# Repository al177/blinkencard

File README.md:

# blinkencard
FPGA based blinky computer emulator

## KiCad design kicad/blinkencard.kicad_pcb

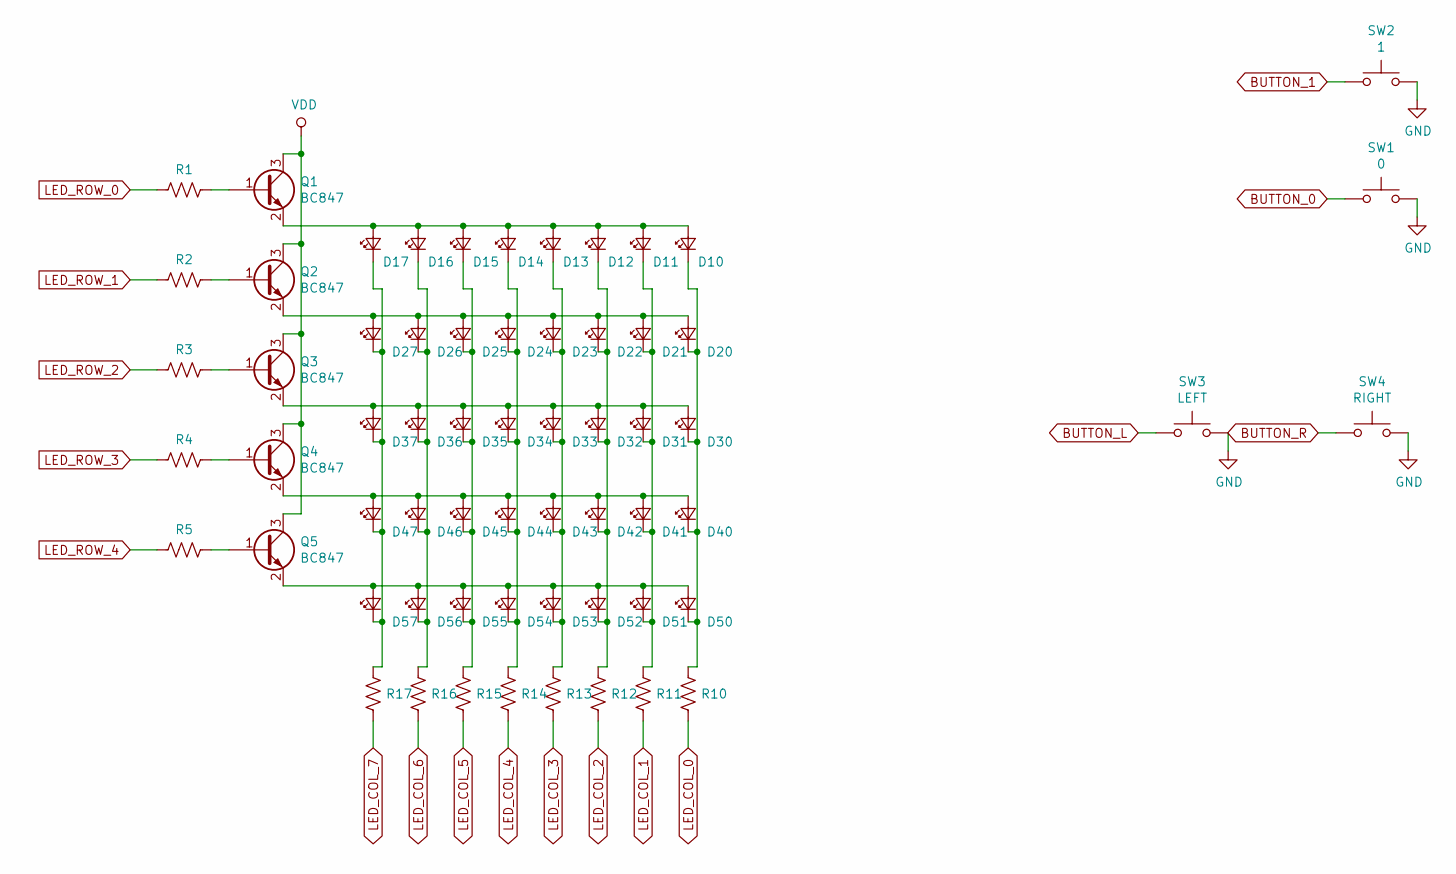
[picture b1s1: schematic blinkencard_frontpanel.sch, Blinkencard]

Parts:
D10, D11, D12, D13, D14, D15, D16, D17, D20, D21, D22, D23, D24, D25, D26, D27, D30, D31, D32, D33, D34, D35, D36, D37, D40, D41, D42, D43, D44, D45, D46, D47, D50, D51, D52, D53, D54, D55, D56, D57: LED_Small; LED_1206_3216Metric_ReverseMount_Hole1.8x2.4mm; mfg_part LTST-C230KRKT
Q1, Q2, Q3, Q4, Q5: BC847; SOT-23; mfg_part BC847CLT1G
R1, R2, R3, R4, R5: 10K; R_0603_1608Metric; mfg_part RC0603JR-0710KL
R10, R11, R12, R13, R14, R15, R16, R17: 270; R_0603_1608Metric; mfg_part RMCF0603JT270R
SW1: 0; SW_SPST_PTS645; mfg_part PTS645SM50SMTR92 LFS
SW2: 1; SW_SPST_PTS645; mfg_part PTS645SM50SMTR92 LFS
SW3: LEFT; SW_SPST_PTS645; mfg_part PTS645SM50SMTR92 LFS
SW4: RIGHT; SW_SPST_PTS645; mfg_part PTS645SM50SMTR92 LFS

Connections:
BUTTON_0: SW1.1; also elsewhere on the board
BUTTON_1: SW2.1; also elsewhere on the board
BUTTON_L: SW3.1; also elsewhere on the board
BUTTON_R: SW4.1; also elsewhere on the board
GND: SW1.2, SW2.2, SW3.2, SW4.2; also elsewhere on the board
LED_COL_0: R10.2; also elsewhere on the board
LED_COL_1: R11.2; also elsewhere on the board
LED_COL_2: R12.2; also elsewhere on the board
LED_COL_3: R13.2; also elsewhere on the board
LED_COL_4: R14.2; also elsewhere on the board
LED_COL_5: R15.2; also elsewhere on the board
LED_COL_6: R16.2; also elsewhere on the board
LED_COL_7: R17.2; also elsewhere on the board
LED_ROW_0: R1.2; also elsewhere on the board
LED_ROW_1: R2.2; also elsewhere on the board
LED_ROW_2: R3.2; also elsewhere on the board
LED_ROW_3: R4.2; also elsewhere on the board
LED_ROW_4: R5.2; also elsewhere on the board
unnamed: D10.1 (K), D20.1 (K), D30.1 (K), D40.1 (K), D50.1 (K), R10.1
unnamed: D10.2 (A), D11.2 (A), D12.2 (A), D13.2 (A), D14.2 (A), D15.2 (A), D16.2 (A), D17.2 (A), Q1.2 (E)
unnamed: D11.1 (K), D21.1 (K), D31.1 (K), D41.1 (K), D51.1 (K), R11.1
unnamed: D12.1 (K), D22.1 (K), D32.1 (K), D42.1 (K), D52.1 (K), R12.1
unnamed: D13.1 (K), D23.1 (K), D33.1 (K), D43.1 (K), D53.1 (K), R13.1
unnamed: D14.1 (K), D24.1 (K), D34.1 (K), D44.1 (K), D54.1 (K), R14.1
unnamed: D15.1 (K), D25.1 (K), D35.1 (K), D45.1 (K), D55.1 (K), R15.1
unnamed: D16.1 (K), D26.1 (K), D36.1 (K), D46.1 (K), D56.1 (K), R16.1
unnamed: D17.1 (K), D27.1 (K), D37.1 (K), D47.1 (K), D57.1 (K), R17.1
unnamed: D20.2 (A), D21.2 (A), D22.2 (A), D23.2 (A), D24.2 (A), D25.2 (A), D26.2 (A), D27.2 (A), Q2.2 (E)
unnamed: D30.2 (A), D31.2 (A), D32.2 (A), D33.2 (A), D34.2 (A), D35.2 (A), D36.2 (A), D37.2 (A), Q3.2 (E)
unnamed: D40.2 (A), D41.2 (A), D42.2 (A), D43.2 (A), D44.2 (A), D45.2 (A), D46.2 (A), D47.2 (A), Q4.2 (E)
unnamed: D50.2 (A), D51.2 (A), D52.2 (A), D53.2 (A), D54.2 (A), D55.2 (A), D56.2 (A), D57.2 (A), Q5.2 (E)
unnamed: Q1.1 (B), R1.1
unnamed: Q2.1 (B), R2.1
unnamed: Q3.1 (B), R3.1
unnamed: Q4.1 (B), R4.1
unnamed: Q5.1 (B), R5.1
VDD: Q1.3 (C), Q2.3 (C), Q3.3 (C), Q4.3 (C), Q5.3 (C); also elsewhere on the board

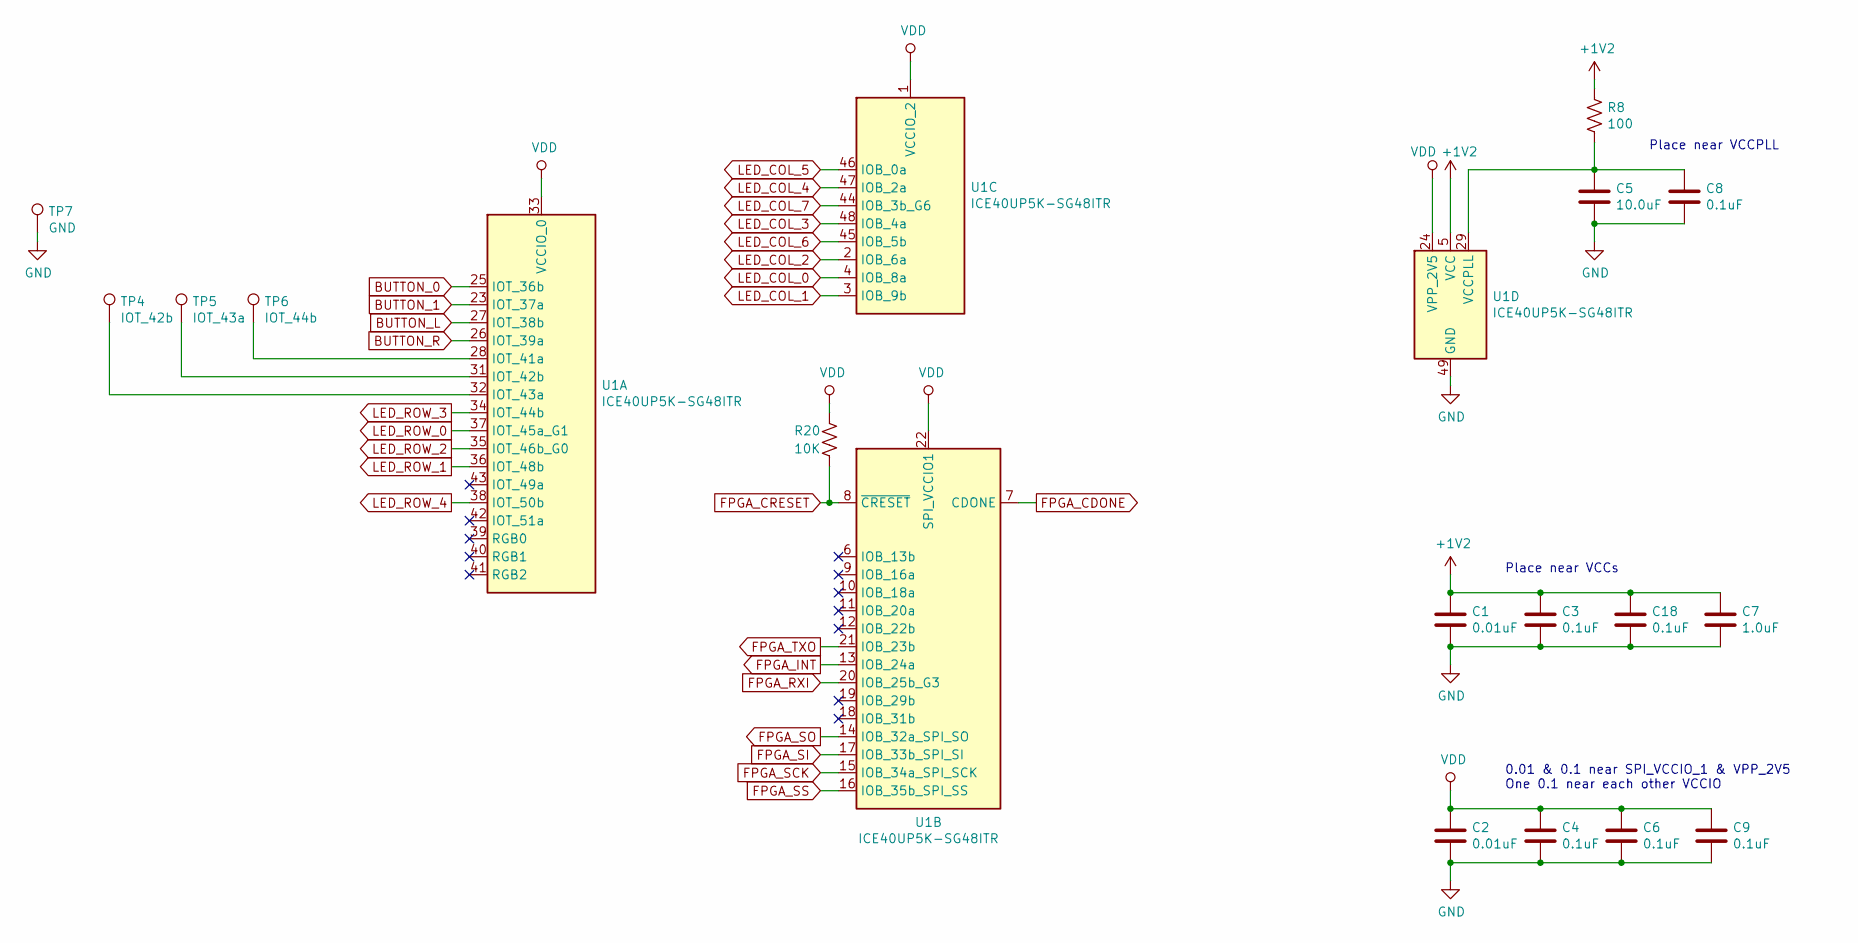
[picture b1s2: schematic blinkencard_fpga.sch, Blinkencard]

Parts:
C1, C2: 0.01uF; C_0603_1608Metric; mfg_part CL21B103KBANNNC
C3, C4, C6, C8, C9, C18: 0.1uF; C_0603_1608Metric; mfg_part CL10F104ZO8NNNC
C5: 10.0uF; C_0805_2012Metric; mfg_part CL21A106KQCLRNC
C7: 1.0uF; C_0805_2012Metric; mfg_part CL21B105KOFNNNG
R8: 100; R_0603_1608Metric; mfg_part RC0603JR-07100RL
R20: 10K; R_0603_1608Metric; mfg_part RC0603JR-0710KL
TP4: IOT_42b; TestPoint_Pad_D1.5mm; mfg_part NP
TP5: IOT_43a; TestPoint_Pad_D1.5mm; mfg_part NP
TP6: IOT_44b; TestPoint_Pad_D1.5mm; mfg_part NP
TP7: GND; TestPoint_Pad_D1.5mm; mfg_part NP
U1: ICE40UP5K-SG48ITR; QFN-48-1EP_7x7mm_P0.5mm_EP5.15x5.15mm_ThermalVias; mfg_part ICE40UP5K-SG48I

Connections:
+1V2: C1.1, C3.1, C7.1, C18.1, R8.1, U1.5 (VCC), U1.30 (VCC); also elsewhere on the board
BUTTON_0: U1.25 (IOT_36b); also elsewhere on the board
BUTTON_1: U1.23 (IOT_37a); also elsewhere on the board
BUTTON_L: U1.27 (IOT_38b); also elsewhere on the board
BUTTON_R: U1.26 (IOT_39a); also elsewhere on the board
FPGA_CDONE: U1.7 (CDONE); also elsewhere on the board
FPGA_CRESET: R20.2, U1.8 (~CRESET); also elsewhere on the board
FPGA_INT: U1.13 (IOB_24a); also elsewhere on the board
FPGA_RXI: U1.20 (IOB_25b_G3); also elsewhere on the board
FPGA_SCK: U1.15 (IOB_34a_SPI_SCK); also elsewhere on the board
FPGA_SI: U1.17 (IOB_33b_SPI_SI); also elsewhere on the board
FPGA_SO: U1.14 (IOB_32a_SPI_SO); also elsewhere on the board
FPGA_SS: U1.16 (IOB_35b_SPI_SS); also elsewhere on the board
FPGA_TXO: U1.21 (IOB_23b); also elsewhere on the board
GND: C1.2, C2.2, C3.2, C4.2, C5.2, C6.2, C7.2, C8.2, C9.2, C18.2, TP7.1, U1.49 (GND); also elsewhere on the board
LED_COL_0: U1.4 (IOB_8a); also elsewhere on the board
LED_COL_1: U1.3 (IOB_9b); also elsewhere on the board
LED_COL_2: U1.2 (IOB_6a); also elsewhere on the board
LED_COL_3: U1.48 (IOB_4a); also elsewhere on the board
LED_COL_4: U1.47 (IOB_2a); also elsewhere on the board
LED_COL_5: U1.46 (IOB_0a); also elsewhere on the board
LED_COL_6: U1.45 (IOB_5b); also elsewhere on the board
LED_COL_7: U1.44 (IOB_3b_G6); also elsewhere on the board
LED_ROW_0: U1.37 (IOT_45a_G1); also elsewhere on the board
LED_ROW_1: U1.36 (IOT_48b); also elsewhere on the board
LED_ROW_2: U1.35 (IOT_46b_G0); also elsewhere on the board
LED_ROW_3: U1.34 (IOT_44b); also elsewhere on the board
LED_ROW_4: U1.38 (IOT_50b); also elsewhere on the board
unnamed: C5.1, C8.1, R8.2, U1.29 (VCCPLL)
unnamed: TP4.1, U1.32 (IOT_43a)
unnamed: TP5.1, U1.31 (IOT_42b)
unnamed: TP6.1, U1.28 (IOT_41a)
VDD: C2.1, C4.1, C6.1, C9.1, R20.1, U1.1 (VCCIO_2), U1.22 (SPI_VCCIO1), U1.24 (VPP_2V5), U1.33 (VCCIO_0); also elsewhere on the board

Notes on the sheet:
0.01 & 0.1 near SPI_VCCIO_1 & VPP_2V5 One 0.1 near each other VCCIO
Place near VCCs
Place near VCCPLL

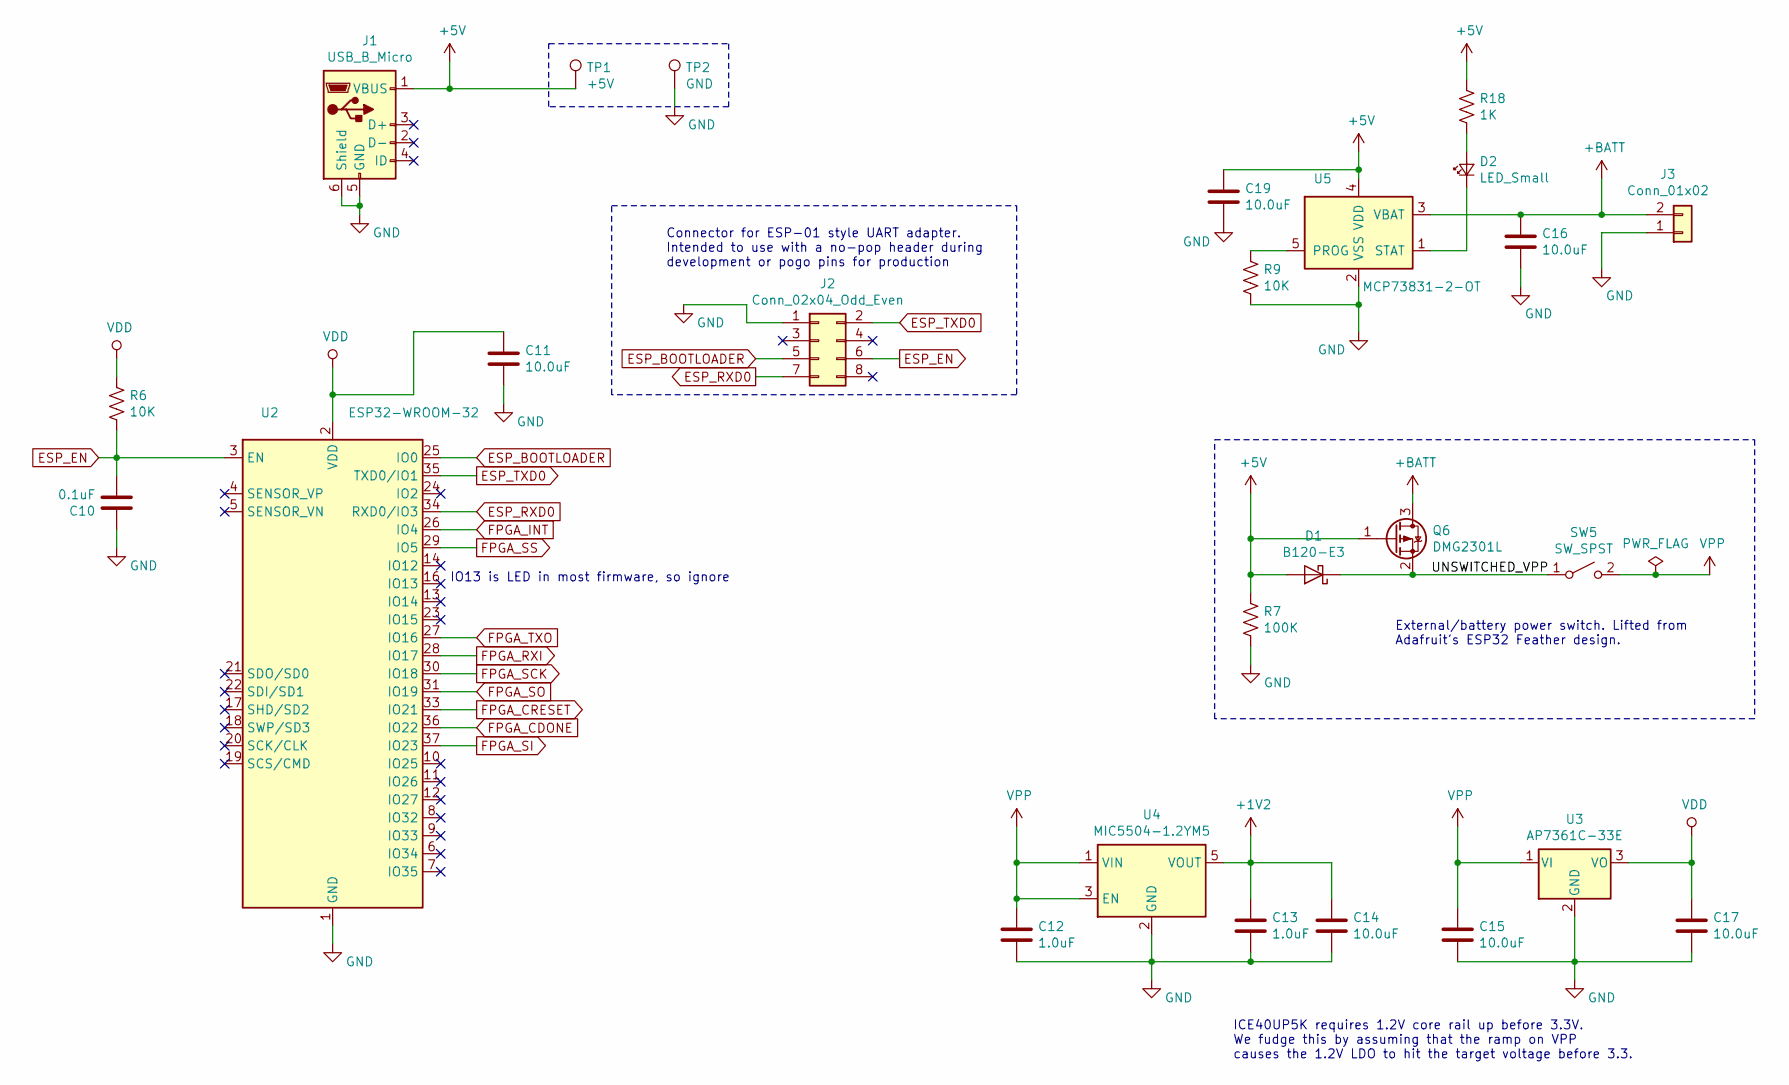
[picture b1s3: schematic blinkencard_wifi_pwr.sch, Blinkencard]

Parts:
C10: 0.1uF; C_0603_1608Metric; mfg_part CL10F104ZO8NNNC
C11, C14, C15, C16, C17, C19: 10.0uF; C_0805_2012Metric; mfg_part CL21A106KQCLRNC
C12, C13: 1.0uF; C_0805_2012Metric; mfg_part CL21B105KOFNNNG
D1: B120-E3; D_SMA; mfg_part B120-E3/61T
D2: LED_Small; LED_0805_2012Metric; mfg_part LTST-S220GKT
J1: USB_B_Micro; USB_Micro-B_Molex-105017-0001; mfg_part 105017-0001
J2: Conn_02x04_Odd_Even; PinHeader_2x04_P2.54mm_Vertical_SMD; mfg_part 54202-S0804LF
J3: Conn_01x02; JST_PH_S2B-PH-SM4-TB_1x02-1MP_P2.00mm_Horizontal; mfg_part S2B-PH-SM4-TB(LF)(SN)
Q6: DMG2301L; SOT-23; mfg_part DMG2301L-7
R6, R9: 10K; R_0603_1608Metric; mfg_part RC0603JR-0710KL
R7: 100K; R_0603_1608Metric; mfg_part RC0603JR-07100KL
R18: 1K; R_0603_1608Metric; mfg_part RC0603JR-071KL
SW5: SW_SPST; SW_SPDT_CK-JS102011SAQN; mfg_part JS102011SAQN
TP1: +5V; TestPoint_Pad_D1.5mm; mfg_part NP
TP2: GND; TestPoint_Pad_D1.5mm; mfg_part NP
U2: ESP32-WROOM-32; mfg_part ESP32-WROOM-32D
U3: AP7361C-33E; SOT-223-3_TabPin2; mfg_part AP7361C-33E-13
U4: MIC5504-1.2YM5; SOT-23-5; mfg_part MIC5504-1.2YM5
U5: MCP73831-2-OT; SOT-23-5; mfg_part MCP73831T-2ATI/OT

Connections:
+1V2: C13.1, C14.1, U4.5 (VOUT); also elsewhere on the board
+5V: C19.1, D1.2 (A), J1.1 (VBUS), Q6.1 (G), R7.1, R18.2, TP1.1, U5.4 (VDD)
+BATT: C16.1, J3.2, Q6.3 (D), U5.3 (VBAT)
/wifi_and_power/UNSWITCHED_VPP: D1.1 (K), Q6.2 (S), SW5.1 (A)
ESP_BOOTLOADER: J2.5, U2.25 (IO0)
ESP_EN: C10.2, J2.6, R6.2, U2.3 (EN)
ESP_RXD0: J2.7, U2.34 (RXD0/IO3)
ESP_TXD0: J2.2, U2.35 (TXD0/IO1)
FPGA_CDONE: U2.36 (IO22); also elsewhere on the board
FPGA_CRESET: U2.33 (IO21); also elsewhere on the board
FPGA_INT: U2.26 (IO4); also elsewhere on the board
FPGA_RXI: U2.28 (IO17); also elsewhere on the board
FPGA_SCK: U2.30 (IO18); also elsewhere on the board
FPGA_SI: U2.37 (IO23); also elsewhere on the board
FPGA_SO: U2.31 (IO19); also elsewhere on the board
FPGA_SS: U2.29 (IO5); also elsewhere on the board
FPGA_TXO: U2.27 (IO16); also elsewhere on the board
GND: C10.1, C11.2, C12.2, C13.2, C14.2, C15.2, C16.2, C17.2, C19.2, J1.5 (GND), J1.6 (Shield), J2.1, J3.1, R7.2, R9.1, TP2.1, U2.1 (GND), U2.15 (GND), U2.38 (GND), U2.39 (GND), U3.2 (GND), U4.2 (GND), U5.2 (VSS); also elsewhere on the board
unnamed: D2.1 (K), U5.1 (STAT)
unnamed: D2.2 (A), R18.1
unnamed: R9.2, U5.5 (PROG)
VDD: C11.1, C17.1, R6.1, U2.2 (VDD), U3.3 (VO); also elsewhere on the board
VPP: C12.1, C15.1, SW5.2 (B), U3.1 (VI), U4.1 (VIN), U4.3 (EN)

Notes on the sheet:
ICE40UP5K requires 1.2V core rail up before 3.3V. We fudge this by assuming that the ramp on VPP causes the 1.2V LDO to hit the target voltage before 3.3.
IO13 is LED in most firmware, so ignore
Connector for ESP-01 style UART adapter. Intended to use with a no-pop header during development or pogo pins for production
External/battery power switch. Lifted from Adafruit's ESP32 Feather design.

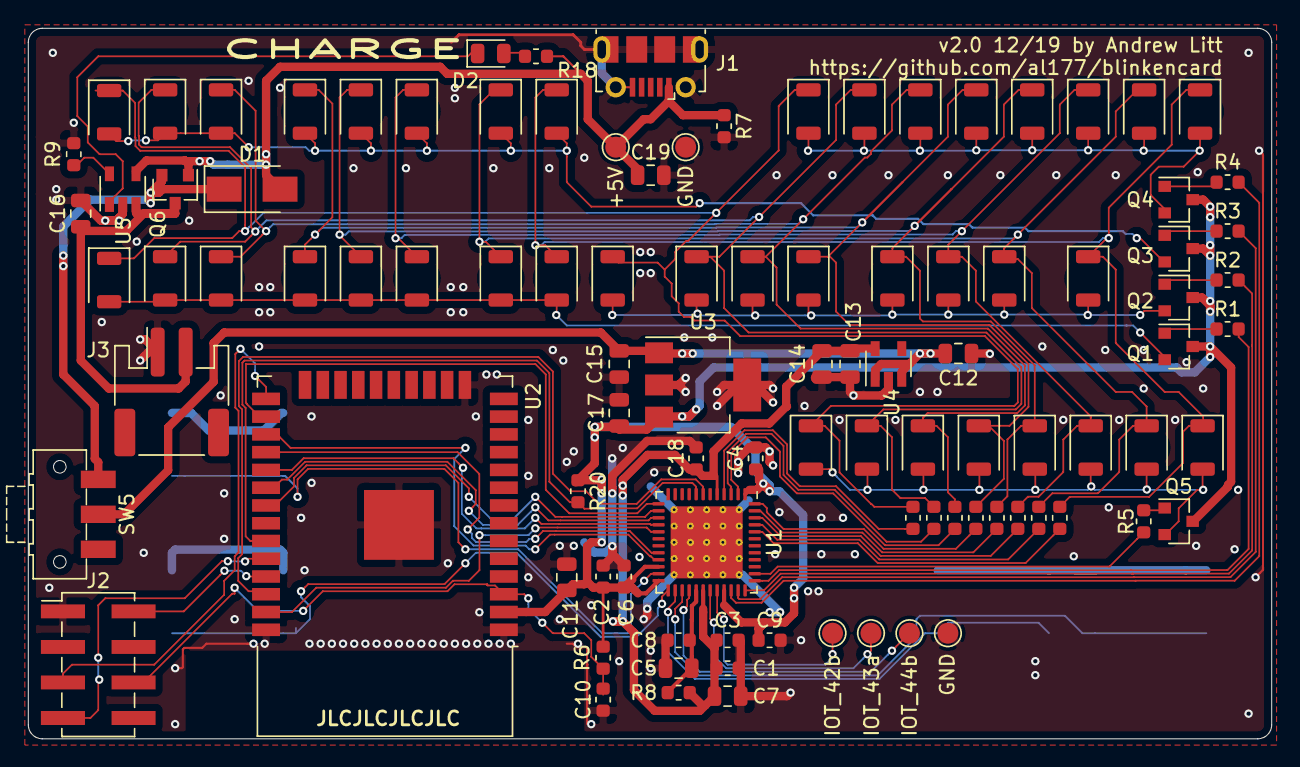
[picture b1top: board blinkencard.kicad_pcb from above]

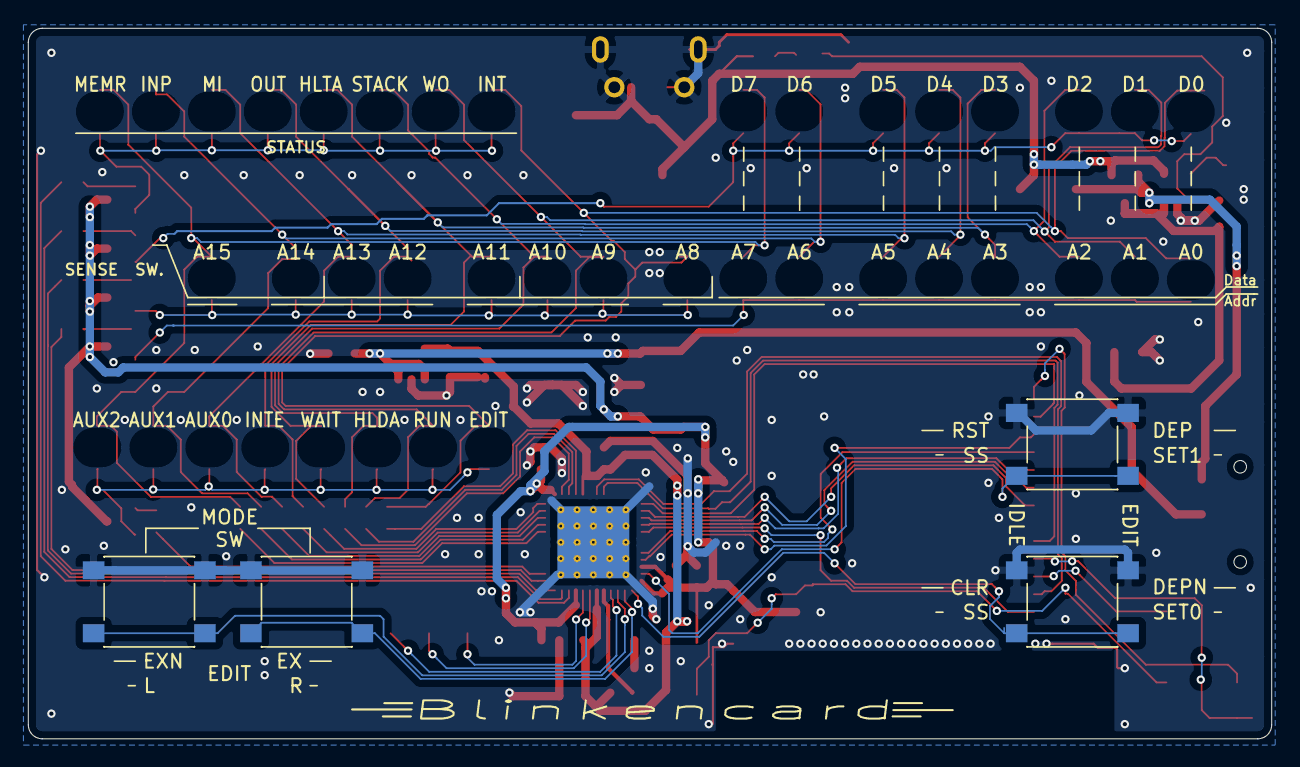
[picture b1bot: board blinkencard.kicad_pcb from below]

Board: 2 copper layers, 88.9 x 50.8 mm, 105 parts (4 on the bottom side), 62 nets.

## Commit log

2019-11-11 Initial add of WIP board
2019-11-11 Add design notes
2019-11-11 LED layout in progress
2019-11-12 More LED routing
2019-11-12 Start routing LEDs. Start ESP32 integration
2019-11-13 Decided to use bottom-firing LEDs. Need to reassign LED refdes
2019-11-15 More flat front panel work
2019-11-16 Use CP2102A USB-UART and GPIO instead of ESP32 to keep it simple. Add power section and start routing.
2019-11-16 LED routing
2019-11-17 Mostly routed
2019-11-17 Routing complete. DRC passes. Need to fix silk around LEDs and do final check
2019-11-17 Fix LED silk, minor routing cleanups
2019-11-18 Refdes silk placement, label cleanup, ground via cleanup
2019-11-18 Move buttons to more sensible locations, finalize silk, tape out v1.0
2019-11-18 Fix minor ground plane issue before submitting v1.0
2019-11-20 Start v1.1 - minor fixes:
    - Replace 4.7uF caps with 10uF
    - Replace 0.01uF cap in the FPGA VCCPLL filter with 10uF per Lattice's design guideline
    - All <1uF caps to 0603 sizes, 1-10uF to 0805
    - Make TP? values match between schem and PCB
    - Sanitize component values for BOM export consistency
2019-11-30 Start v2.0 - change USB-UART to ESP32 and bugfixes
2019-12-02 Finish routing v2.0.
2019-12-03 Fix RESET and GPIO0 (bootload) on the programming header to match an actual ESP-01 programmer
2019-12-05 Finish converting to ESP32, start on adding LiPo power
2019-12-16 First pass routing complete w/ LiPo charging
2019-12-16 Layout complete for v2 build. Needs review.
2019-12-18 Add more sch comments
2019-12-18 Add cap across 5V for charger
2019-12-19 v2.0 release - clean silk, add order number placeholder for JLCPCB, add MFG PN in components for BOM, add BOM, add STEP, generate fab outputs
2019-12-28 Add v2.0 Micropython (LoBoris fork) FPGA loader module and startup script
2020-01-12 Switch to mainline Micropython, so update iceboot for the mainline machine APIs
2020-01-16 Add OpenSCAD case
2020-01-30 Simple serial terminal for talking to the FPGA
2020-02-20 Add some convenience scripts
2020-02-25 First commit of telnet to UART server for Blinkencard
2020-02-25 Case for Blinkencard with a LiPo pouch cell
2020-05-25 Start telnet server on boot. CTRL-A k to exit the telnet server if you want to use REPL
2025-05-23 Add filament handle
2025-05-23 Add debug port cover and reinforce back case
2025-05-25 Slightly thicker case to accomodate 1100mAh 603449 battery
2025-05-25 Loader fix due to new (better) file.read() behavior
2025-05-25 Remove debug print in loader
2025-06-05 Prep for macros
2025-06-17 case: Make plug sturdier and easier to remove
    Add a bridge at the top of the debug plug for lateral stability.
    Also make the removal holes larger to fit more tools.
